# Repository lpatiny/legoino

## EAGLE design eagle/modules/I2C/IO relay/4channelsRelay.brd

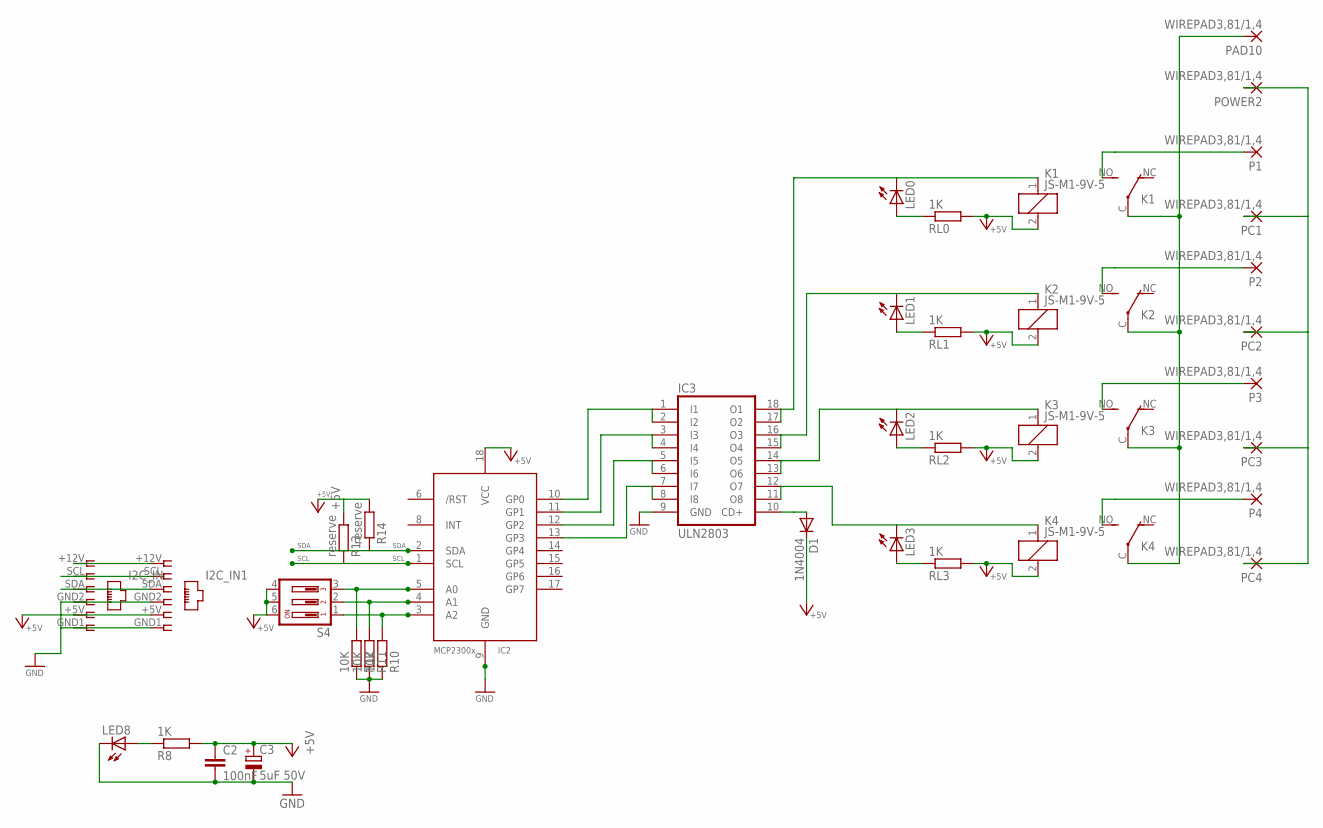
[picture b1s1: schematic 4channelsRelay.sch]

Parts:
C2: 100nF; C1206
C3: 5uF 50V; E3,5-8
D1: 1N4004; DO41-10
I2C_IN: I2C 1; RJ12-STRAIGHT-I2C
I2C_IN1: I2C 2; RJ12-STRAIGHT-I2C
IC2: MCP2300X/P; DIL18
IC3: ULN2803; DIL18
K1, K2, K3, K4: JS-M1-9V-5; JS-M
LED0, LED1, LED2, LED3, LED8: LED3MM
P1, P2, P3, P4: WIREPAD3,81/1,4; 3,81/1,4
PAD10: WIREPAD3,81/1,4; 3,81/1,4
PC1, PC2, PC3, PC4: WIREPAD3,81/1,4; 3,81/1,4
POWER2: WIREPAD3,81/1,4; 3,81/1,4
R8: 1K; M1206
R10, R11, R12: 10K; M1206
R13, R14: reserve; M1206
RL0, RL1, RL2, RL3: 1K; M1206
S4: DIP03YL

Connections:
+5V: C2.1, C3.+, D1.C, I2C_IN.+5V (5), I2C_IN1.+5V (5), IC2.18 (VCC), K1.2, K2.2, K3.2, K4.2, R8.2, R13.2, R14.2, RL0.2, RL1.2, RL2.2, RL3.2, S4.4, S4.5, S4.6
CD+: D1.A, IC3.10 (CD+)
GND: C2.2, C3.-, I2C_IN.GND1 (6), I2C_IN.GND2 (4), I2C_IN1.GND1 (6), I2C_IN1.GND2 (4), IC2.9 (GND), IC3.9 (GND), LED8.K (C), R10.1, R11.1, R12.1
unnamed: IC3.15 (O4), IC3.16 (O3), K2.1, LED1.K (C)
unnamed: LED0.A, RL0.1
unnamed: IC3.17 (O2), IC3.18 (O1), K1.1, LED0.K (C)
unnamed: LED1.A, RL1.1
unnamed: I2C_IN.+12V (1), I2C_IN1.+12V (1)
unnamed: K4.NO (S), P4.1
unnamed: IC3.11 (O8), IC3.12 (O7), K4.1, LED3.K (C)
unnamed: K3.NO (S), P3.1
unnamed: PC1.1, PC2.1, PC3.1, PC4.1, POWER2.1
unnamed: K2.NO (S), P2.1
unnamed: IC2.5 (A0), R12.2, S4.3
unnamed: IC2.4 (A1), R11.2, S4.2
unnamed: IC2.3 (A2), R10.2, S4.1
unnamed: K1.NO (S), P1.1
unnamed: LED8.A, R8.1
unnamed: LED2.A, RL2.1
unnamed: IC3.13 (O6), IC3.14 (O5), K3.1, LED2.K (C)
unnamed: LED3.A, RL3.1
P0: IC2.10 (GP0), IC3.1 (I1), IC3.2 (I2)
P1: IC2.11 (GP1), IC3.3 (I3), IC3.4 (I4)
P2: IC2.12 (GP2), IC3.5 (I5), IC3.6 (I6)
P3: IC2.13 (GP3), IC3.7 (I7), IC3.8 (I8)
POWER1: K1.C, K2.C, K3.C, K4.C, PAD10.1
SCL: I2C_IN.SCL (2), I2C_IN1.SCL (2), IC2.1 (SCL), R13.1
SDA: I2C_IN.SDA (3), I2C_IN1.SDA (3), IC2.2 (SDA), R14.1

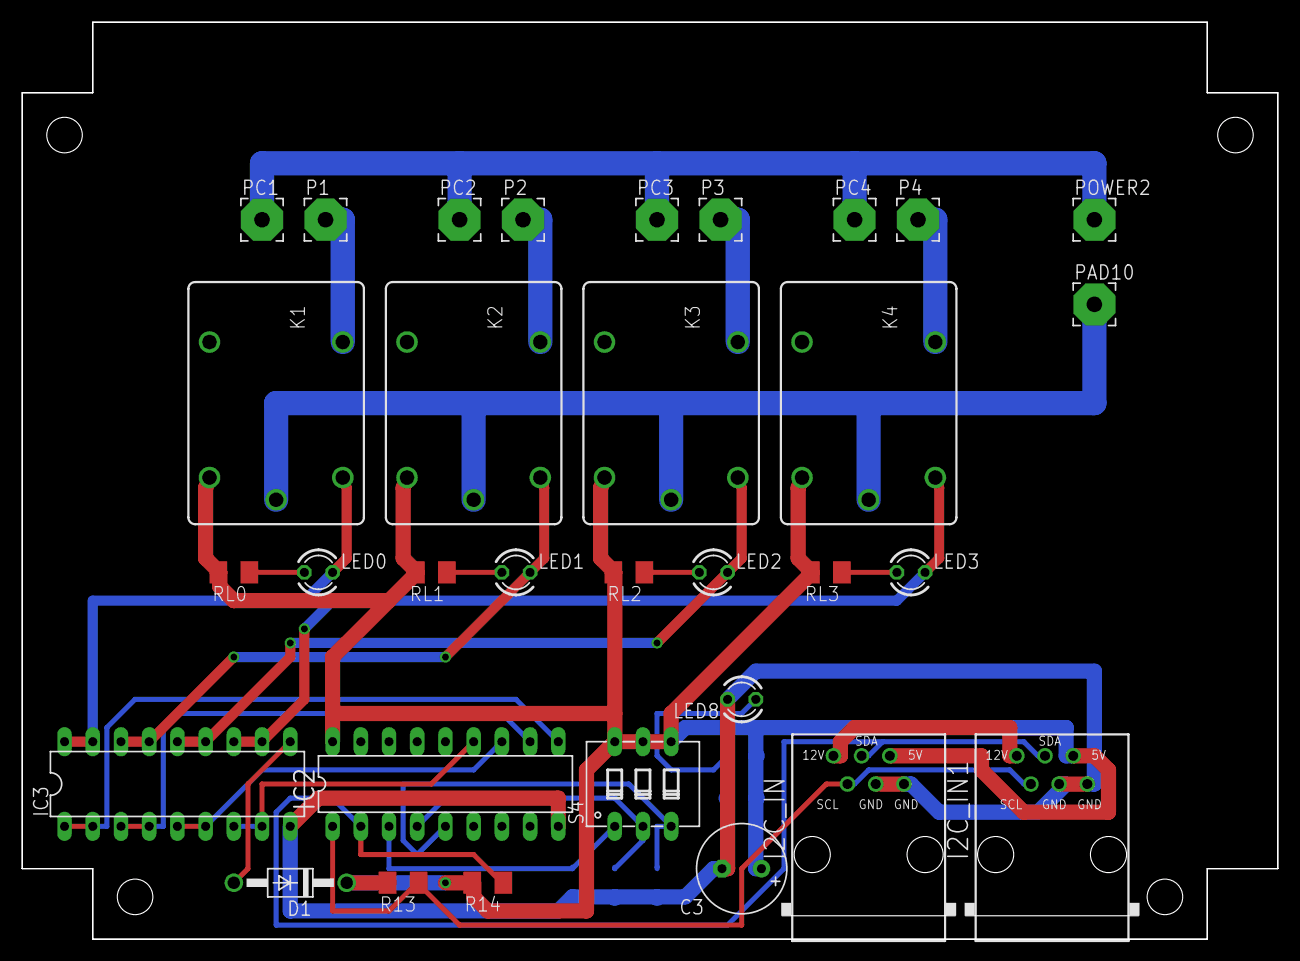
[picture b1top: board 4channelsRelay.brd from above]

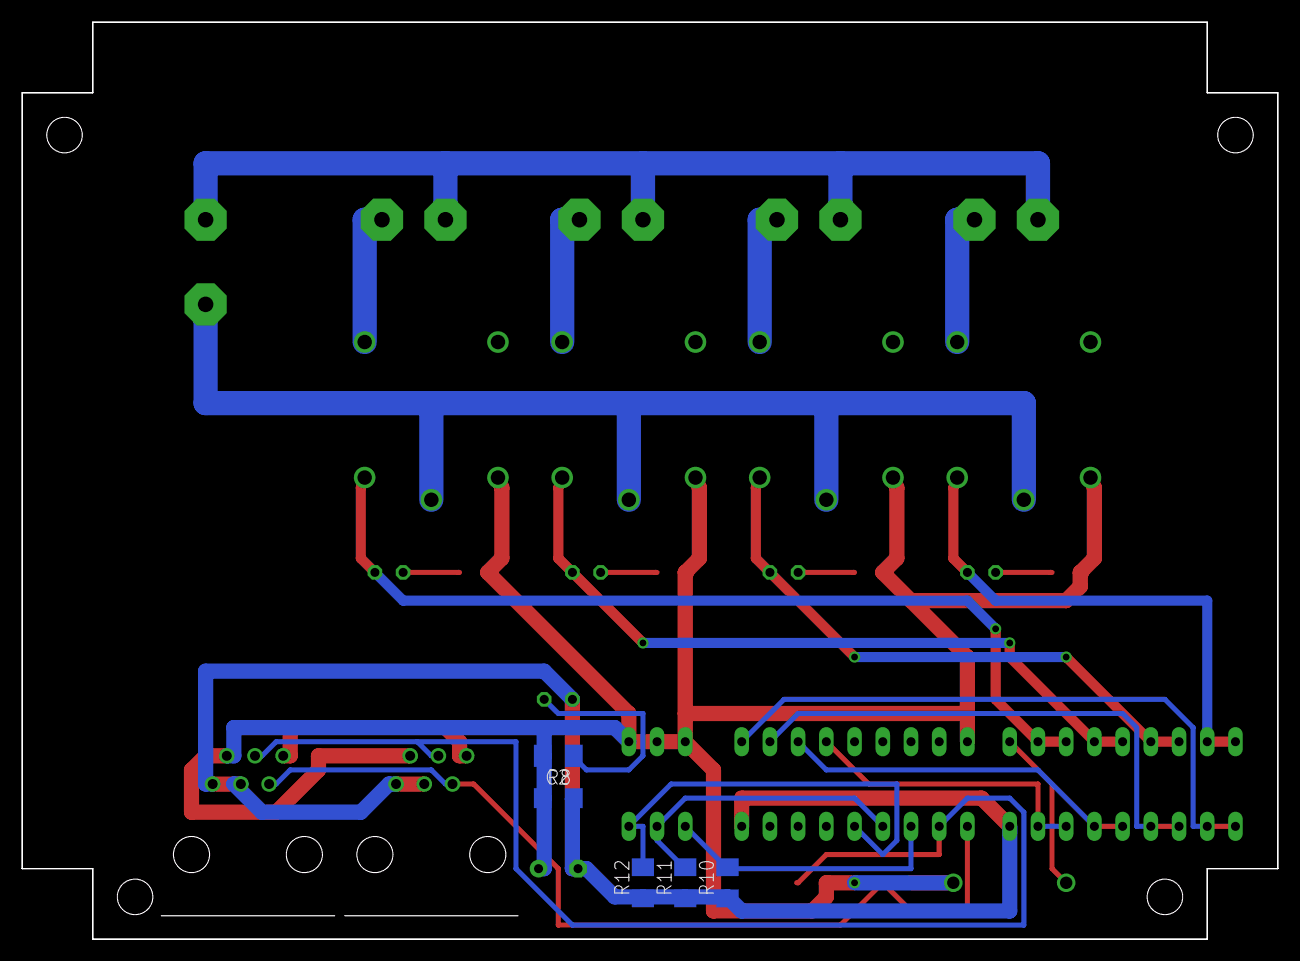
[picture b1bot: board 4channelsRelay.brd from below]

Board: 2 copper layers, 113.0 x 82.5 mm, 37 parts (5 on the bottom side), 28 nets.

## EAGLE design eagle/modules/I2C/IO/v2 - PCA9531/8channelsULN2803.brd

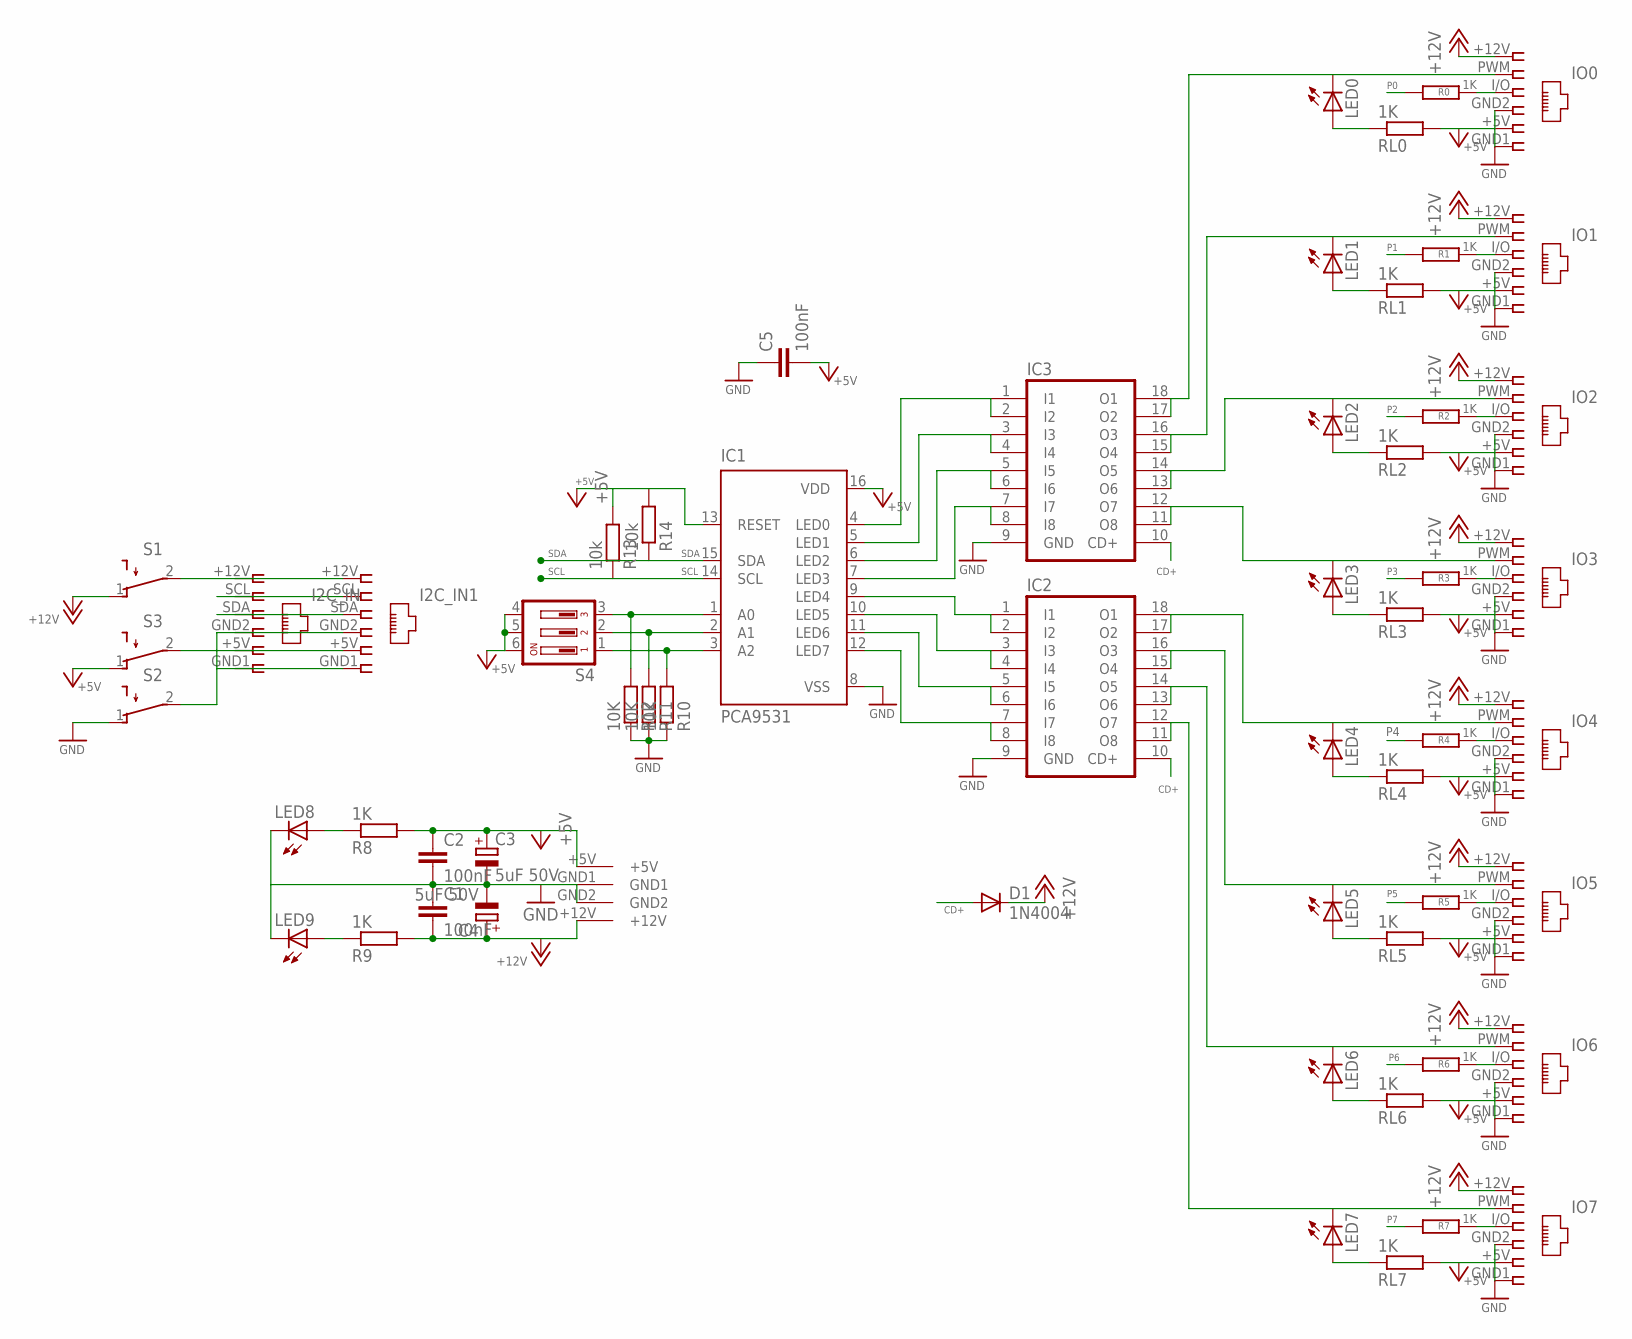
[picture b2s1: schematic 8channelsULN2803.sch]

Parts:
C1, C2, C5: 100nF; C1206
C3, C4: 5uF 50V; E3,5-8
D1: 1N4004; DO41-10
I2C_IN: I2C 1; RJ12-STRAIGHT-I2C
I2C_IN1: I2C 2; RJ12-STRAIGHT-I2C
IC1: PCA9531; SO16
IC2, IC3: ULN2803A; DIL18
IO0: IO0; RJ12-STRAIGHT
IO1: IO1; RJ12-STRAIGHT
IO2: IO2; RJ12-STRAIGHT
IO3: IO3; RJ12-STRAIGHT
IO4: IO4; RJ12-STRAIGHT
IO5: IO5; RJ12-STRAIGHT
IO6: IO6; RJ12-STRAIGHT
IO7: IO7; RJ12-STRAIGHT
LED0, LED1, LED2, LED3, LED4, LED5, LED6, LED7, LED8, LED9: LED3MM
R0, R1, R2, R3, R4, R5, R6, R7, R8, R9: 1K; M1206
R10, R11, R12: 10K; M1206
R13, R14: 10k; M1206
RL0, RL1, RL2, RL3, RL4, RL5, RL6, RL7: 1K; M1206
S1, S3: SWITCHSWITCH; SWITCH2
S2: SWITCHPAD; PADS2
S4: DIP03YL
U$2: KPJX-4S-S

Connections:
+5V: C2.1, C3.+, C5.2, IC1.13 (RESET), IC1.16 (VDD), IO0.+5V (5), IO1.+5V (5), IO2.+5V (5), IO3.+5V (5), IO4.+5V (5), IO5.+5V (5), IO6.+5V (5), IO7.+5V (5), R8.2, R13.2, R14.2, RL0.2, RL1.2, RL2.2, RL3.2, RL4.2, RL5.2, RL6.2, RL7.2, S3.1 (O), S4.4, S4.5, S4.6, U$2.+5V
+12V: C1.2, C4.+, D1.C, IO0.+12V (1), IO1.+12V (1), IO2.+12V (1), IO3.+12V (1), IO4.+12V (1), IO5.+12V (1), IO6.+12V (1), IO7.+12V (1), R9.2, S1.1 (O), U$2.+12V
CD+: D1.A, IC2.10 (CD+), IC3.10 (CD+)
D2B: IO4.I/O (3), R4.1
D2B1: IO5.I/O (3), R5.1
D2B2: IO6.I/O (3), R6.1
D2B3: IO7.I/O (3), R7.1
D2B4: IO0.I/O (3), R0.1
D2B5: IO1.I/O (3), R1.1
D2B6: IO2.I/O (3), R2.1
D2B7: IO3.I/O (3), R3.1
GND: C1.1, C2.2, C3.-, C4.-, C5.1, IC1.8 (VSS), IC2.9 (GND), IC3.9 (GND), IO0.GND1 (6), IO0.GND2 (4), IO1.GND1 (6), IO1.GND2 (4), IO2.GND1 (6), IO2.GND2 (4), IO3.GND1 (6), IO3.GND2 (4), IO4.GND1 (6), IO4.GND2 (4), IO5.GND1 (6), IO5.GND2 (4), IO6.GND1 (6), IO6.GND2 (4), IO7.GND1 (6), IO7.GND2 (4), LED8.K (C), LED9.K (C), R10.1, R11.1, R12.1, S2.1 (O), U$2.GND1, U$2.GND2
unnamed: IC3.15 (O4), IC3.16 (O3), IO1.PWM (2), LED1.K (C)
unnamed: LED0.A, RL0.1
unnamed: IC3.17 (O2), IC3.18 (O1), IO0.PWM (2), LED0.K (C)
unnamed: LED1.A, RL1.1
unnamed: I2C_IN.+12V (1), I2C_IN1.+12V (1), S1.2
unnamed: IC2.13 (O6), IC2.14 (O5), IO6.PWM (2), LED6.K (C)
unnamed: I2C_IN.+5V (5), I2C_IN1.+5V (5), S3.2
unnamed: IC2.17 (O2), IC2.18 (O1), IO4.PWM (2), LED4.K (C)
unnamed: IC3.11 (O8), IC3.12 (O7), IO3.PWM (2), LED3.K (C)
unnamed: I2C_IN.GND1 (6), I2C_IN.GND2 (4), I2C_IN1.GND1 (6), I2C_IN1.GND2 (4), S2.2
unnamed: LED5.A, RL5.1
unnamed: LED9.A, R9.1
unnamed: LED4.A, RL4.1
unnamed: IC1.1 (A0), R12.2, S4.3
unnamed: IC1.2 (A1), R11.2, S4.2
unnamed: IC1.3 (A2), R10.2, S4.1
unnamed: LED6.A, RL6.1
unnamed: LED8.A, R8.1
unnamed: LED7.A, RL7.1
unnamed: LED2.A, RL2.1
unnamed: IC3.13 (O6), IC3.14 (O5), IO2.PWM (2), LED2.K (C)
unnamed: LED3.A, RL3.1
unnamed: IC2.15 (O4), IC2.16 (O3), IO5.PWM (2), LED5.K (C)
unnamed: IC2.11 (O8), IC2.12 (O7), IO7.PWM (2), LED7.K (C)
P0: IC1.4 (LED0), IC3.1 (I1), IC3.2 (I2), R0.2
P1: IC1.5 (LED1), IC3.3 (I3), IC3.4 (I4), R1.2
P2: IC1.6 (LED2), IC3.5 (I5), IC3.6 (I6), R2.2
P3: IC1.7 (LED3), IC3.7 (I7), IC3.8 (I8), R3.2
P4: IC1.9 (LED4), IC2.1 (I1), IC2.2 (I2), R4.2
P5: IC1.10 (LED5), IC2.3 (I3), IC2.4 (I4), R5.2
P6: IC1.11 (LED6), IC2.5 (I5), IC2.6 (I6), R6.2
P7: IC1.12 (LED7), IC2.7 (I7), IC2.8 (I8), R7.2
SCL: I2C_IN.SCL (2), I2C_IN1.SCL (2), IC1.14 (SCL), R13.1
SDA: I2C_IN.SDA (3), I2C_IN1.SDA (3), IC1.15 (SDA), R14.1

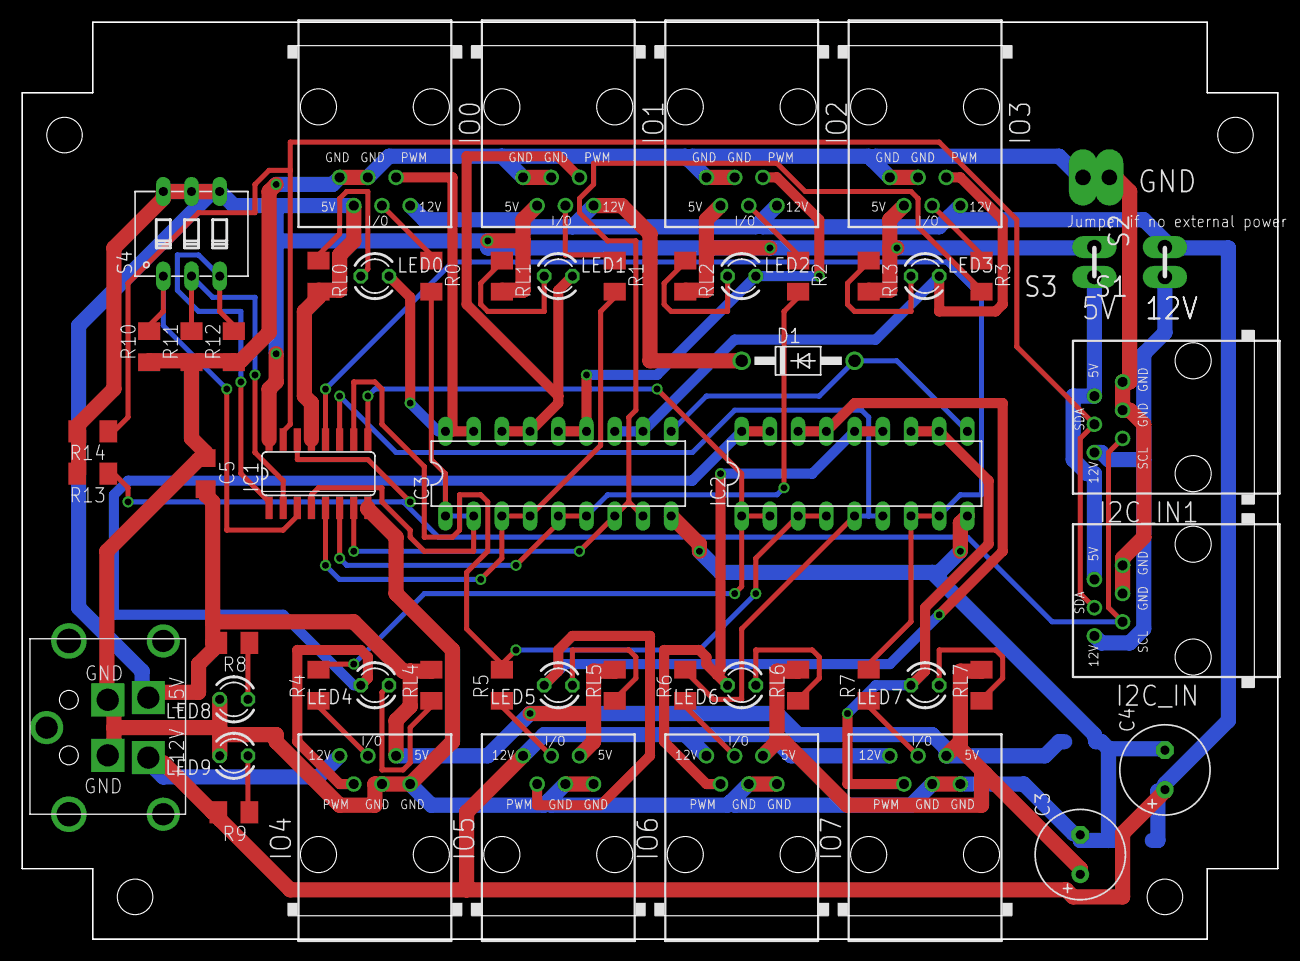
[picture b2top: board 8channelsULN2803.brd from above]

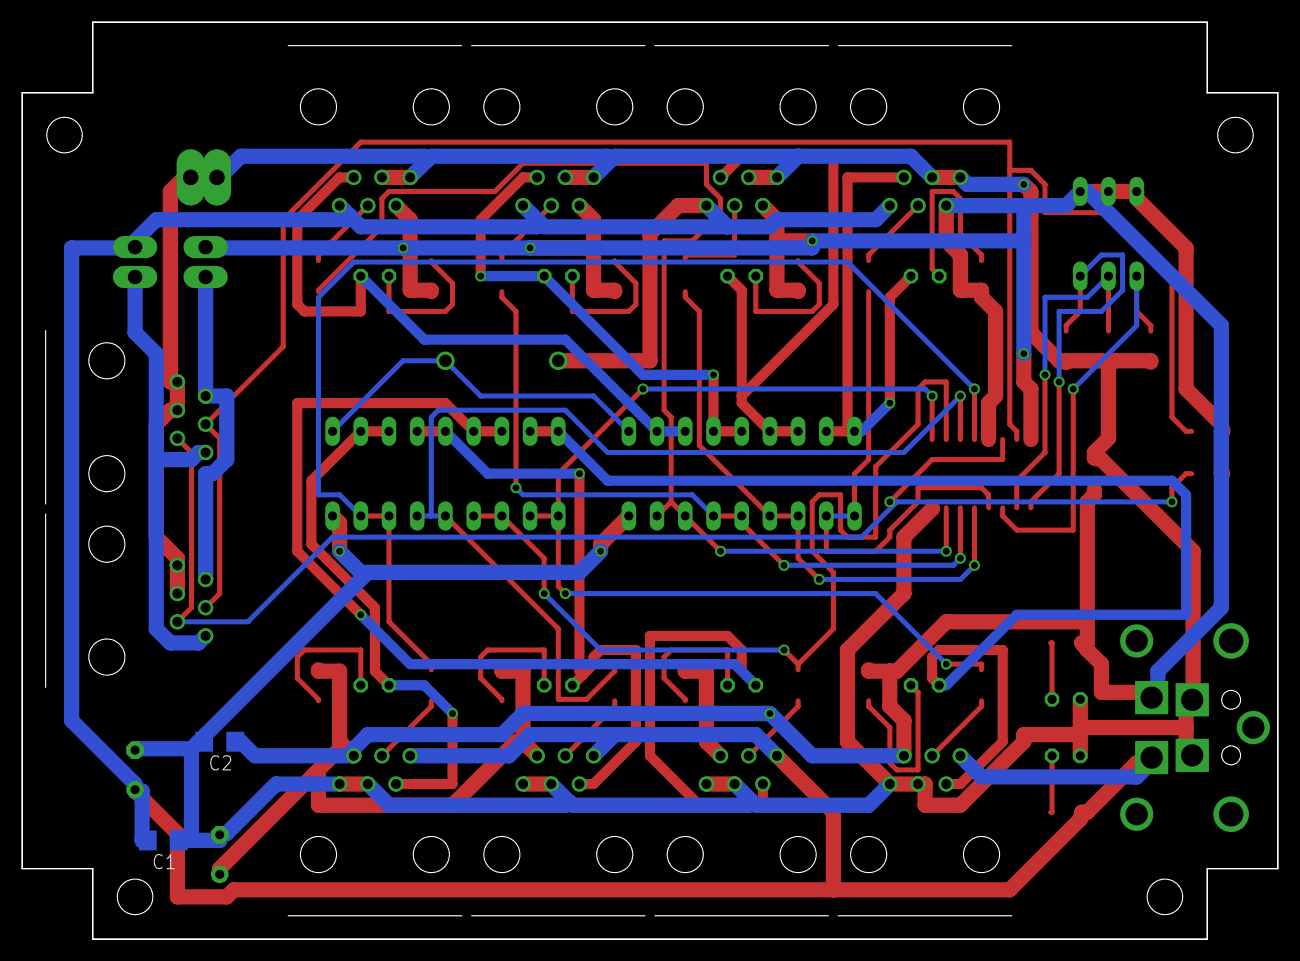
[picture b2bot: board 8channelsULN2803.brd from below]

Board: 2 copper layers, 113.0 x 82.5 mm, 57 parts (2 on the bottom side), 46 nets.

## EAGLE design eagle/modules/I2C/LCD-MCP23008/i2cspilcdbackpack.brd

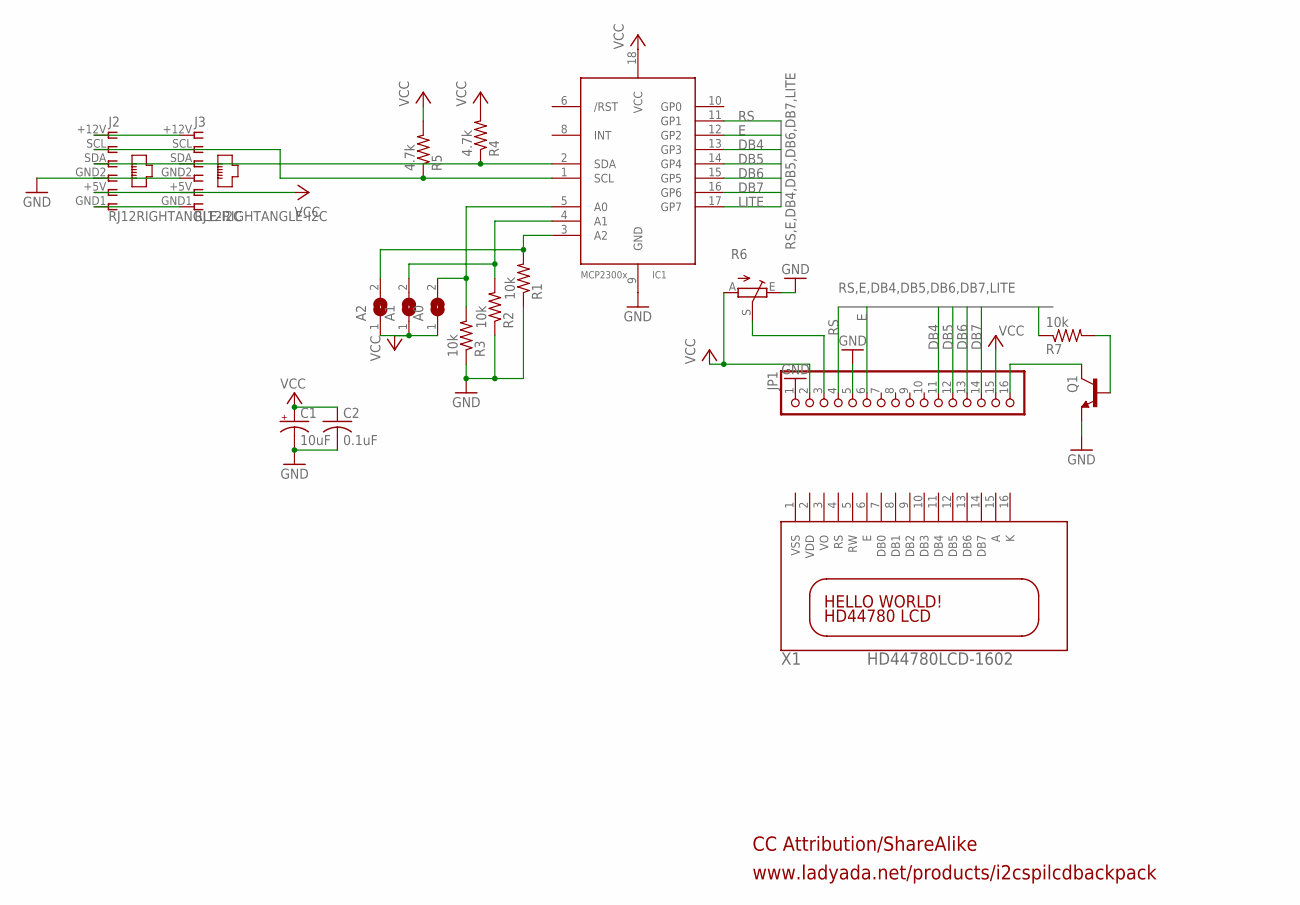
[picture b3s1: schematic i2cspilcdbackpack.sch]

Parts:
A0, A1, A2: SJ
C1: 10uF; A/3216-18R
C2: 0.1uF; C1206
IC1: MCP2300X/P; DIL18
J2, J3: RJ12RIGHTANGLE-I2C; RJ12-RIGHTANGLE-I2C
JP1: PINHD-1X16; 1X16
Q1: MMBT2222ALT1-NPN-SOT23-BEC; SOT23-BEC
R1, R2, R3, R7: 10k; M1206
R4, R5: 4.7k; M1206
R6: TRIM_EU-CA9V; CA9V
X1: HD44780LCD-1602; LCD1602

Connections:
CLOCK: IC1.1 (SCL), J2.SCL (2), J3.SCL (2), R5.1
DATA: IC1.2 (SDA), J2.SDA (3), J3.SDA (3), R4.1
DB4: IC1.13 (GP3), JP1.11
DB5: IC1.14 (GP4), JP1.12
DB6: IC1.15 (GP5), JP1.13
DB7: IC1.16 (GP6), JP1.14
E: IC1.12 (GP2), JP1.6
GND: C1.-, C2.2, IC1.9 (GND), J2.GND2 (4), J3.GND2 (4), JP1.1, JP1.5, Q1.E, R1.1, R2.1, R3.1, R6.E
LITE: IC1.17 (GP7), R7.1
unnamed: A0.2, IC1.5 (A0), R3.2
unnamed: A1.2, IC1.4 (A1), R2.2
unnamed: A2.2, IC1.3 (A2), R1.2
unnamed: J2.+12V (1), J3.+12V (1)
unnamed: JP1.16, Q1.C
unnamed: Q1.B, R7.2
unnamed: JP1.3, R6.S
unnamed: J2.GND1 (6), J3.GND1 (6)
RS: IC1.11 (GP1), JP1.4
VCC: A0.1, A1.1, A2.1, C1.+, C2.1, IC1.18 (VCC), J2.+5V (5), J3.+5V (5), JP1.2, JP1.15, R4.2, R5.2, R6.A

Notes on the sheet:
www.ladyada.net/products/i2cspilcdbackpack
CC Attribution/ShareAlike

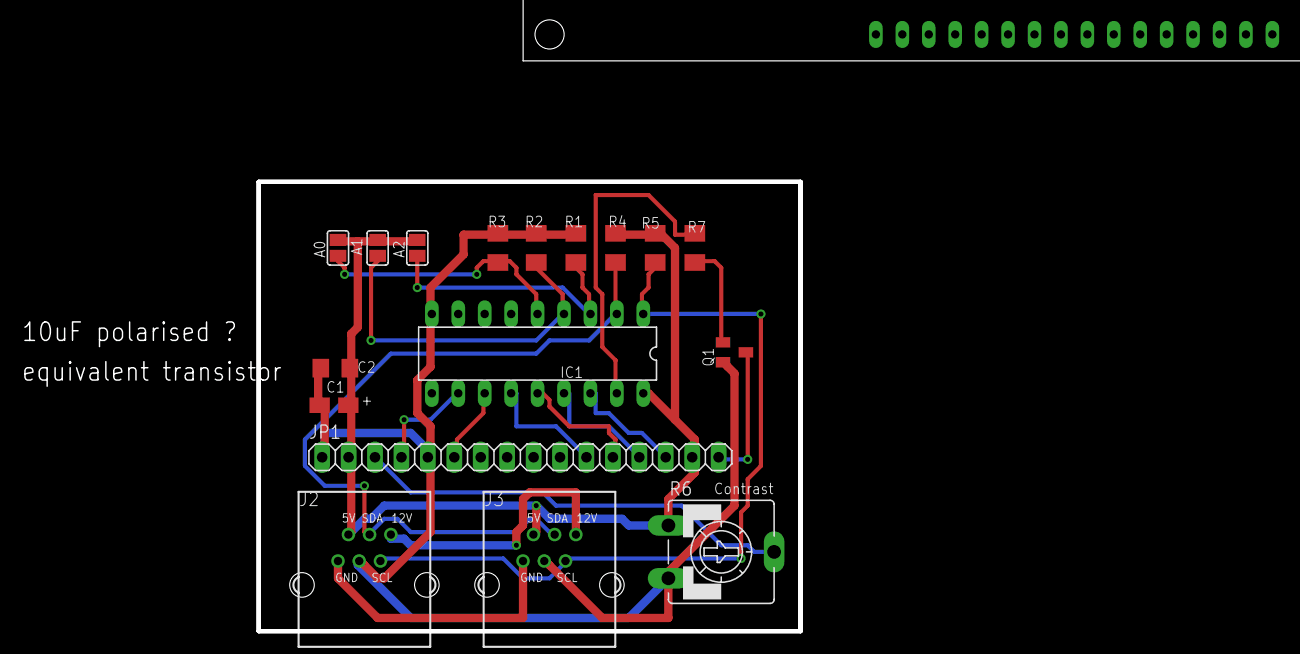
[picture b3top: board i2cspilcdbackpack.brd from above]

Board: 2 copper layers, 52.1 x 43.2 mm, 18 parts (0 on the bottom side), 19 nets.

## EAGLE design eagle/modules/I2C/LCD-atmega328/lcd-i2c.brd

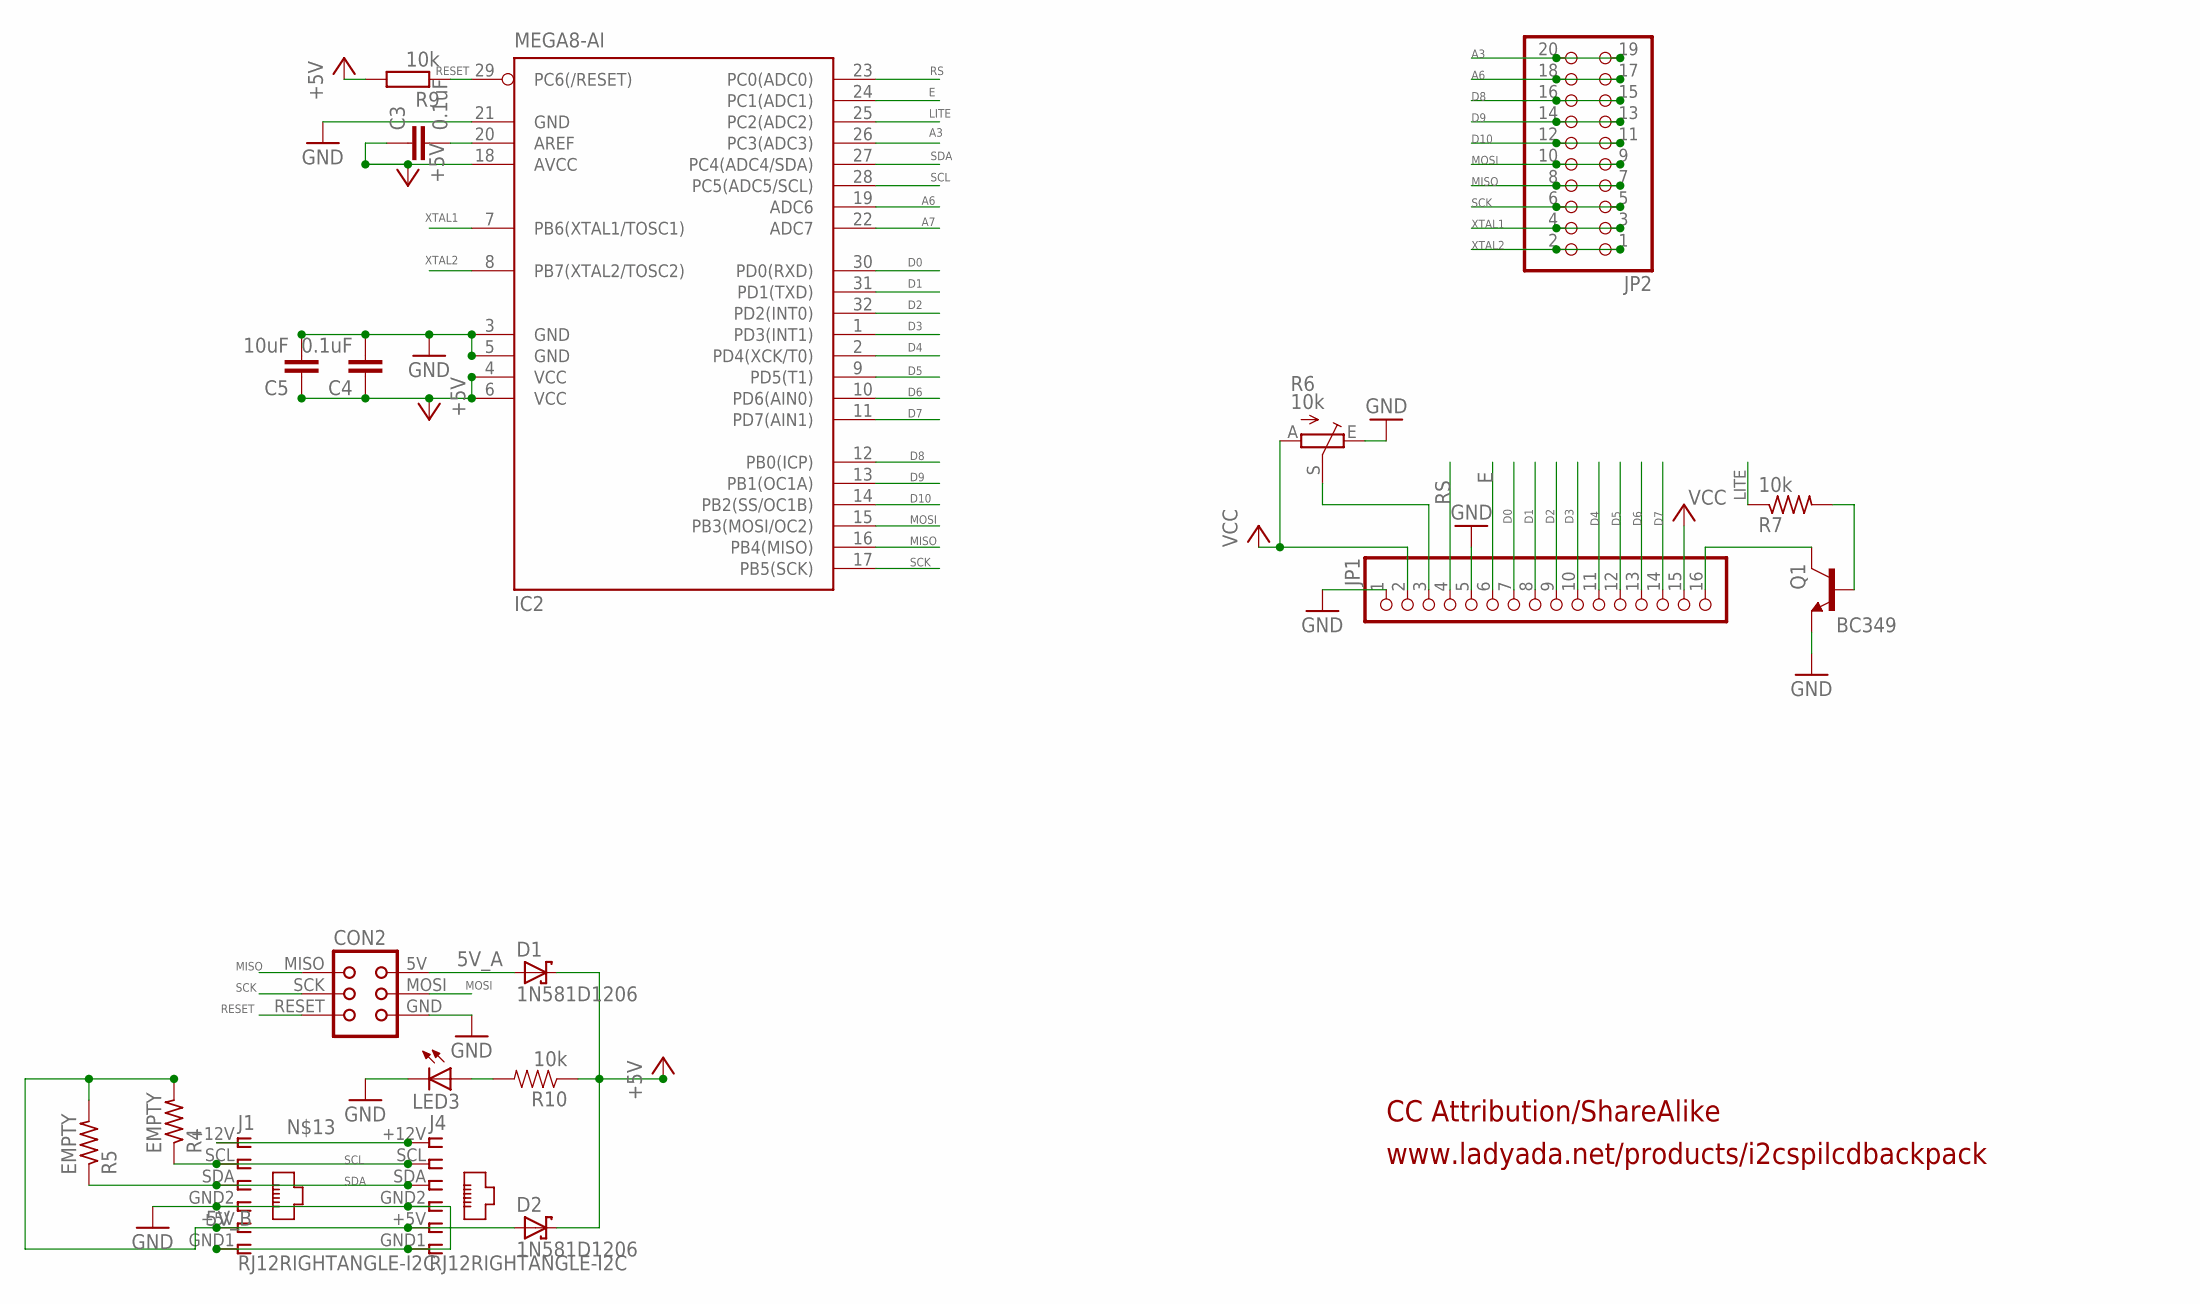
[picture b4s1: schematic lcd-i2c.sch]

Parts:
C3, C4: 0.1uF; C1206
C5: 10uF; C1206
CON2: TINYISPTAG; TC2030-MCP
D1, D2: 1N581D1206; LED-1206
IC2: MEGA8-AI; TQFP32-08
J1, J4: RJ12RIGHTANGLE-I2C; RJ12-RIGHTANGLE-I2C
JP1: PINHD-1X16; 1X16
JP2: PINHD-2X10; 2X10
LED3: LEDCHIP-LED0603; CHIP-LED0603
Q1: BC349; TO92-EBC
R4, R5: EMPTY; M1206
R6: 10k; CA6V
R7, R9: 10k; M1206
R10: 10k; 0603-RES

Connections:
5V_A: CON2.5V (VCC), D1.A
5V_B: D2.A, J1.+5V (5), J4.+5V (5), R4.2, R5.2
+5V: C3.1, C4.1, C5.1, D1.C, D2.C, IC2.4 (VCC), IC2.6 (VCC), IC2.18 (AVCC), R9.2, R10.1
A3: IC2.26 (PC3(ADC3)), JP2.19, JP2.20
A6: IC2.19 (ADC6), JP2.17, JP2.18
A7: IC2.22 (ADC7)
D0: IC2.30 (PD0(RXD)), JP1.7
D1: IC2.31 (PD1(TXD)), JP1.8
D2: IC2.32 (PD2(INT0)), JP1.9
D3: IC2.1 (PD3(INT1)), JP1.10
D4: IC2.2 (PD4(XCK/T0)), JP1.11
D5: IC2.9 (PD5(T1)), JP1.12
D6: IC2.10 (PD6(AIN0)), JP1.13
D7: IC2.11 (PD7(AIN1)), JP1.14
D8: IC2.12 (PB0(ICP)), JP2.15, JP2.16
D9: IC2.13 (PB1(OC1A)), JP2.13, JP2.14
D10: IC2.14 (PB2(SS/OC1B)), JP2.11, JP2.12
E: IC2.24 (PC1(ADC1)), JP1.6
GND: C4.2, C5.2, CON2.GND, IC2.3 (GND), IC2.5 (GND), IC2.21 (GND), J1.GND1 (6), J1.GND2 (4), J4.GND1 (6), J4.GND2 (4), JP1.1, JP1.5, LED3.C, Q1.E, R6.E
LITE: IC2.25 (PC2(ADC2)), R7.1
MISO: CON2.MISO, IC2.16 (PB4(MISO)), JP2.7, JP2.8
MOSI: CON2.MOSI, IC2.15 (PB3(MOSI/OC2)), JP2.9, JP2.10
unnamed: C3.2, IC2.20 (AREF)
unnamed: JP1.16, Q1.C
unnamed: Q1.B, R7.2
unnamed: JP1.3, R6.S
unnamed: J1.+12V (1), J4.+12V (1)
unnamed: LED3.A, R10.2
RESET: CON2.RESET, IC2.29 (PC6(/RESET)), R9.1
RS: IC2.23 (PC0(ADC0)), JP1.4
SCK: CON2.SCK, IC2.17 (PB5(SCK)), JP2.5, JP2.6
SCL: IC2.28 (PC5(ADC5/SCL)), J1.SCL (2), J4.SCL (2), R4.1
SDA: IC2.27 (PC4(ADC4/SDA)), J1.SDA (3), J4.SDA (3), R5.1
VCC: JP1.2, JP1.15, R6.A
XTAL1: IC2.7 (PB6(XTAL1/TOSC1)), JP2.3, JP2.4
XTAL2: IC2.8 (PB7(XTAL2/TOSC2)), JP2.1, JP2.2

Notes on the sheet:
www.ladyada.net/products/i2cspilcdbackpack
CC Attribution/ShareAlike

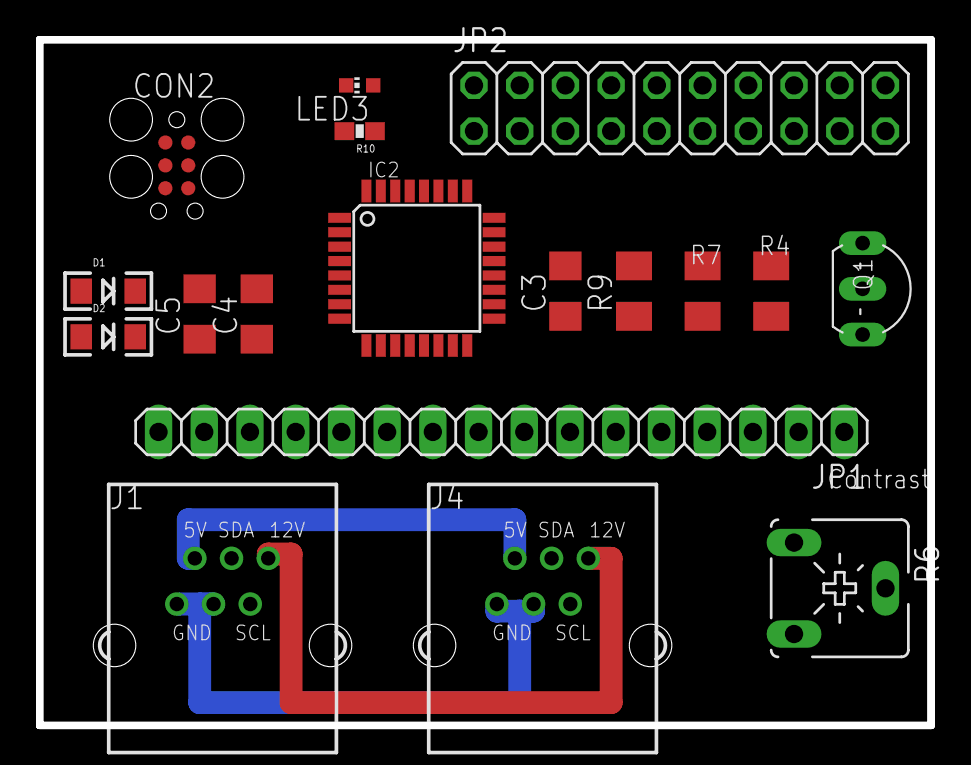
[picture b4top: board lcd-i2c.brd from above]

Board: 2 copper layers, 49.5 x 38.1 mm, 19 parts (1 on the bottom side), 35 nets.

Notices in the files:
parts and their libraries:
lpatiny: ©2009 ROFA.cz - modified and updated by Robert Darlington ‹rdarlington@gmail.com›
SparkFun: Licensing: CC v3.0 Share-Alike You are welcome to use this library for commercial purposes.
